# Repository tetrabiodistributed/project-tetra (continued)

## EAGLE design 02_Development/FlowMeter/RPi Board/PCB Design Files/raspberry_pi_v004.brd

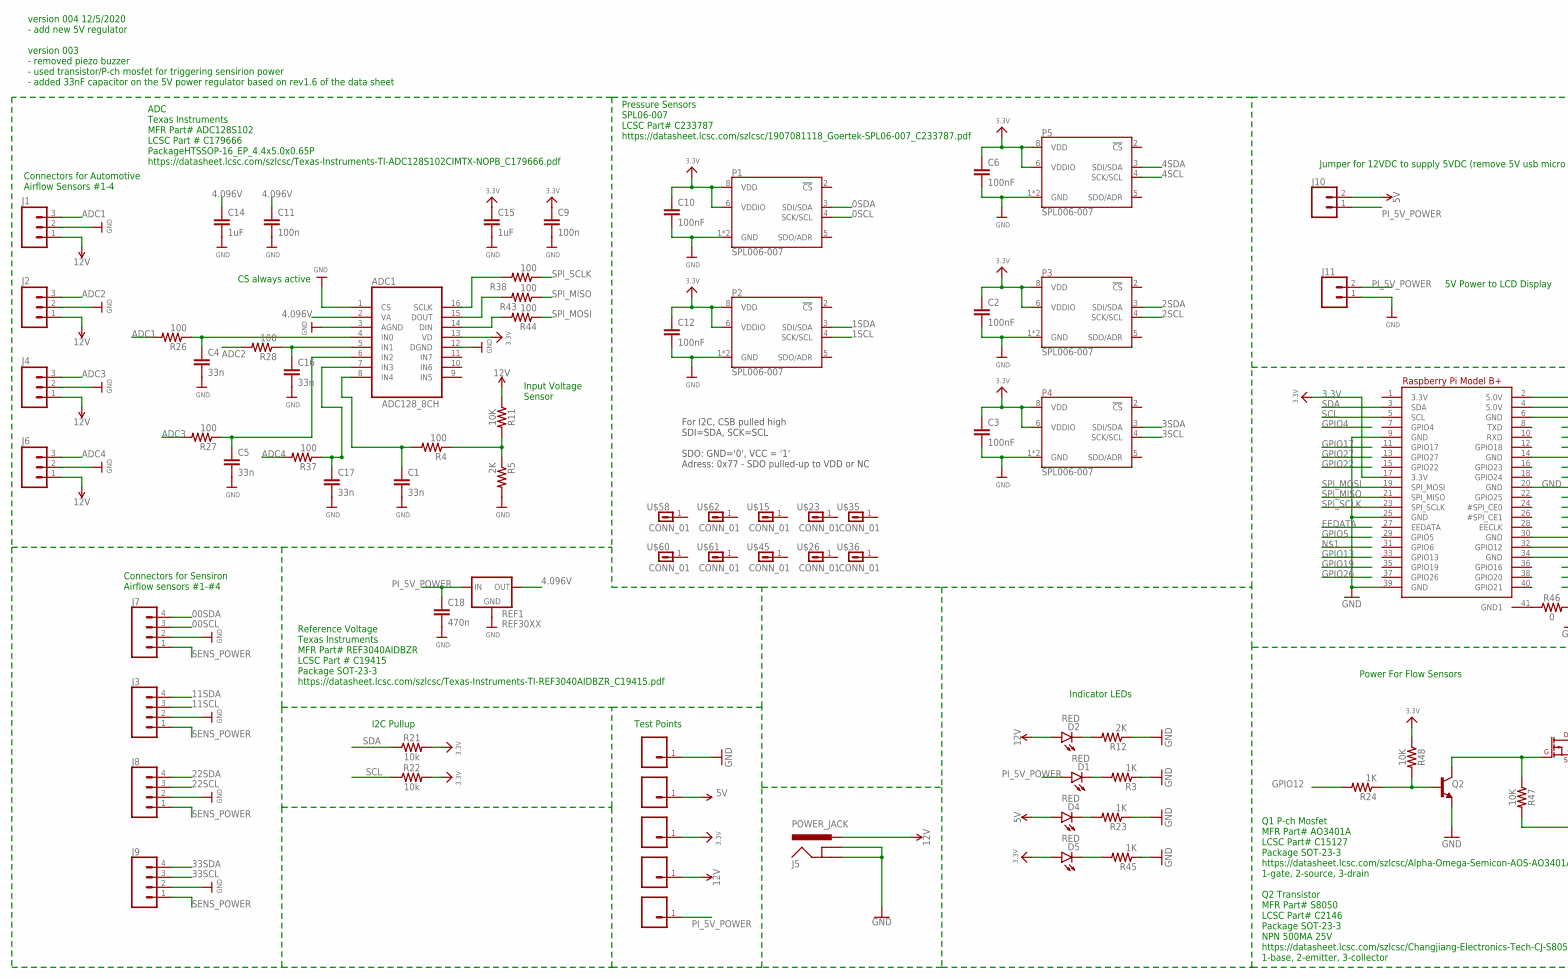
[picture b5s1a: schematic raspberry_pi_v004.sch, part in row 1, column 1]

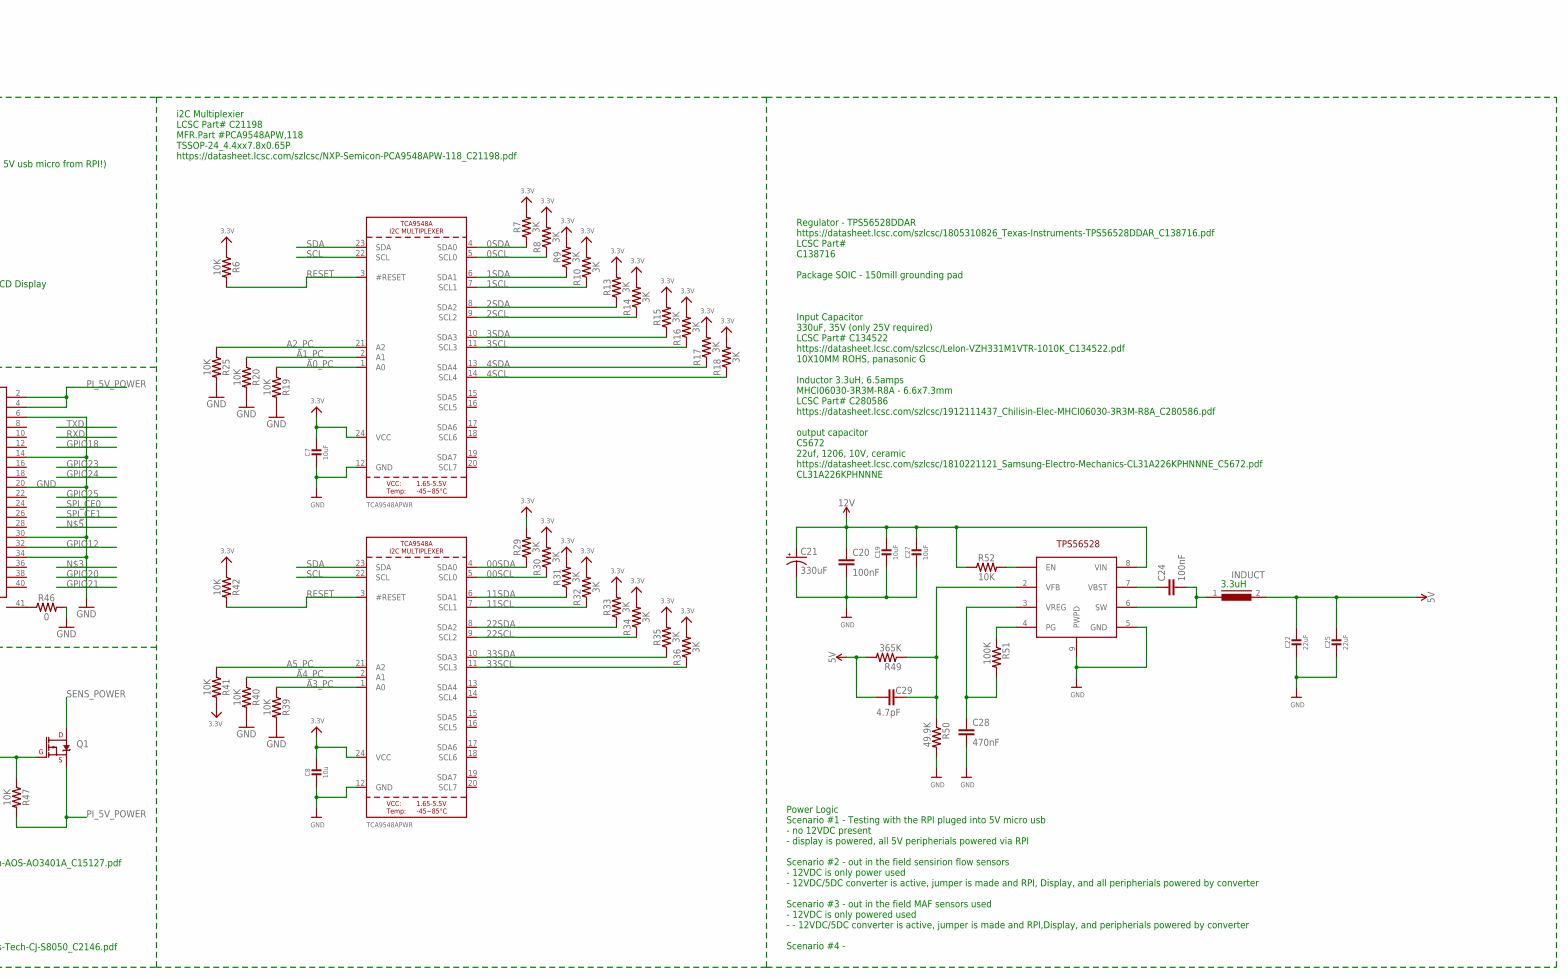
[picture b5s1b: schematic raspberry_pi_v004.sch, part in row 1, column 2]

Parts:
ADC1: ADC128_8CH; TSSOP16
C1, C4, C5, C16, C17: 33n; 0805
C2, C3, C6, C10, C12, C20, C24: 100nF; 0805
C7, C19, C27: 10uF; 0805-NO
C8: 10u; 0805-NO
C9, C11: 100n; 0805
C14, C15: 1uF; 0805
C18: 470n; 0805
C21: 330uF; PANASONIC_G
C22, C25: 22uF; _1206
C28: 470nF; 0805
C29: 4.7pF; 0603
D1, D2, D4, D5: RED; LED-1206
INDUCT: INDUCTOR_6.6_7.3
J1, J2, J4, J6: M03SCREW; SCREWTERMINAL-3.5MM-3
J3, J7, J8, J9: CONN_043.5MM_RA; 1X04_3.5MM_RA
J5: POWER_JACK; POWER_JACK_PTH
J10: CONN_02; 1X02
J11: CONN_025MM; SCREWTERMINAL-5MM-2
P1, P2, P3, P4, P5: SPL006-007; LGA-8-2.5X2.0
Q1: 4.3A/20V/54mΩ; SOT23-3
Q2: 500mA/300V; SOT23-3
R3, R23, R24, R45: 1K; 0805
R4, R26, R27, R28, R37, R38, R43, R44: 100; 0805
R5, R12: 2K; 0805
R6, R11, R19, R20, R25, R39, R40, R41, R42, R47, R48, R52: 10K; 0805
R7, R8, R9, R10, R13, R14, R15, R16, R17, R18, R29, R30, R31, R32, R33, R34, R35, R36: 3K; 0805
R21, R22: 10k; 0805
R46: 0; 0805
R49: 365K; 0805
R50: 49.9K; 0805
R51: 100K; 0805
REF1: REF30XX; SOT23-3
RPI2: MICROBUILDER_RASPBERRYPI_BPLUS_HATSLOTS; MICROBUILDER_PI_HAT_SLOTS
TPS: TPS56528; SOIC8_POWER
U6, U7: TCA9548APWR; TSSOP24
U$15, U$23, U$26, U$35, U$36, U$45, U$58, U$60, U$61, U$62: CONN_01; 1X01-#6_MACHINE
U$20, U$31, U$40, U$59, U$64: CONN_0138MILL; 1X01-40MILL

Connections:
0SCL: P1.4 (SCK/SCL), R8.1, U6.5 (SCL0)
00SCL: J7.3, R30.1, U7.5 (SCL0)
0SDA: P1.3 (SDI/SDA), R7.1, U6.4 (SDA0)
00SDA: J7.4, R29.1, U7.4 (SDA0)
1SCL: P2.4 (SCK/SCL), R10.1, U6.7 (SCL1)
1SDA: P2.3 (SDI/SDA), R9.1, U6.6 (SDA1)
2SCL: P3.4 (SCK/SCL), R14.1, U6.9 (SCL2)
2SDA: P3.3 (SDI/SDA), R13.1, U6.8 (SDA2)
3.3V: ADC1.13 (VD), C2.1, C3.1, C6.1, C7.1, C8.1, C9.1, C10.1, C12.1, C15.1, D5.A, P1.6 (VDDIO), P1.8 (VDD), P2.6 (VDDIO), P2.8 (VDD), P3.6 (VDDIO), P3.8 (VDD), P4.6 (VDDIO), P4.8 (VDD), P5.6 (VDDIO), P5.8 (VDD), R6.1, R7.2, R8.2, R9.2, R10.2, R13.2, R14.2, R15.2, R16.2, R17.2, R18.2, R21.2, R22.2, R29.2, R30.2, R31.2, R32.2, R33.2, R34.2, R35.2, R36.2, R41.2, R42.1, R48.1, RPI2.17 (3.3V), U6.24 (VCC), U7.24 (VCC), U$20.1
3SCL: P4.4 (SCK/SCL), R16.1, U6.11 (SCL3)
3SDA: P4.3 (SDI/SDA), R15.1, U6.10 (SDA3)
4.096V: ADC1.2 (VA), C11.1, C14.1, REF1.2 (OUT)
4SCL: P5.4 (SCK/SCL), R18.1, U6.14 (SCL4)
4SDA: P5.3 (SDI/SDA), R17.1, U6.13 (SDA4)
5V: C22.1, C25.1, C29.1, D4.A, INDUCT.2, J10.2, R49.2, U$59.1
11SCL: J3.3, R32.1, U7.7 (SCL1)
11SDA: J3.4, R31.1, U7.6 (SDA1)
12V: C19.1, C20.1, C21.+, C27.1, D2.A, J1.1, J2.1, J4.1, J5.PWR, J6.1, R11.1, R52.1, TPS.8 (VIN), U$40.1
22SCL: J8.3, R34.1, U7.9 (SCL2)
22SDA: J8.4, R33.1, U7.8 (SDA2)
33SCL: J9.3, R36.1, U7.11 (SCL3)
33SDA: J9.4, R35.1, U7.10 (SDA3)
A0_PC: R19.1, U6.1 (A0)
A1_PC: R20.1, U6.2 (A1)
A2_PC: R25.1, U6.21 (A2)
A3_PC: R39.1, U7.1 (A0)
A4_PC: R40.1, U7.2 (A1)
A5_PC: R41.1, U7.21 (A2)
ADC1: J1.3, R26.2
ADC2: J2.3, R28.2
ADC3: J4.3, R27.2
ADC4: J6.3, R37.2
GND: ADC1.1 (CS), ADC1.3 (AGND), ADC1.12 (DGND), C1.2, C2.2, C3.2, C4.2, C5.2, C6.2, C7.2, C8.2, C9.2, C10.2, C11.2, C12.2, C14.2, C15.2, C16.2, C17.2, C18.2, C19.2, C20.2, C21.-, C22.2, C25.2, C27.2, C28.2, J1.2, J2.2, J3.2, J4.2, J5.GND, J5.GNDBREAK, J6.2, J7.2, J8.2, J9.2, J11.1, P1.1 (GND), P1.7 (GND), P2.1 (GND), P2.7 (GND), P3.1 (GND), P3.7 (GND), P4.1 (GND), P4.7 (GND), P5.1 (GND), P5.7 (GND), Q2.2 (E), R3.1, R5.2, R12.1, R19.2, R20.2, R23.1, R25.2, R39.2, R40.2, R45.1, R46.2, R50.2, REF1.3 (GND), RPI2.6 (GND), RPI2.9 (GND), RPI2.14 (GND), RPI2.20 (GND), RPI2.25 (GND), RPI2.30 (GND), RPI2.34 (GND), RPI2.39 (GND), TPS.5 (GND), TPS.9 (PWPD), U6.12 (GND), U7.12 (GND), U$31.1
GND1: R46.1, RPI2.41 (GND1)
GPIO12: R24.2, RPI2.32 (GPIO12)
unnamed: D2.C, R12.2
unnamed: C24.2, INDUCT.1, TPS.6 (SW)
unnamed: C28.1, R51.2, TPS.3 (VREG)
unnamed: D1.C, R3.2
unnamed: Q1.1 (G), Q2.3 (C), R47.1
unnamed: Q2.1 (B), R24.1, R48.2
unnamed: C29.2, R49.1, R50.1, TPS.2 (VFB)
unnamed: ADC1.8 (IN4), C1.1, R4.2
unnamed: R4.1, R5.1, R11.2
unnamed: C24.1, TPS.7 (VBST)
unnamed: D4.C, R23.2
unnamed: D5.C, R45.2
unnamed: R51.1, TPS.4 (PG)
unnamed: ADC1.4 (IN0), C4.1, R26.1
unnamed: ADC1.6 (IN2), C5.1, R27.1
unnamed: ADC1.5 (IN1), C16.1, R28.1
unnamed: ADC1.7 (IN3), C17.1, R37.1
unnamed: ADC1.16 (SCLK), R38.2
unnamed: ADC1.15 (DOUT), R43.2
unnamed: ADC1.14 (DIN), R44.2
unnamed: R52.2, TPS.1 (EN)
PI_5V_POWER: C18.1, D1.A, J10.1, J11.2, Q1.2 (S), R47.2, REF1.1 (IN), RPI2.2 (5.0V), RPI2.4 (5.0V), U$64.1
RESET: R6.2, R42.2, U6.3 (#RESET), U7.3 (#RESET)
SCL: R22.1, RPI2.5 (SCL), U6.22 (SCL), U7.22 (SCL)
SDA: R21.1, RPI2.3 (SDA), U6.23 (SDA), U7.23 (SDA)
SENS_POWER: J3.1, J7.1, J8.1, J9.1, Q1.3 (D)
SPI_MISO: R43.1, RPI2.21 (SPI_MISO)
SPI_MOSI: R44.1, RPI2.19 (SPI_MOSI)
SPI_SCLK: R38.1, RPI2.23 (SPI_SCLK)

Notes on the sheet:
I2C Pullup
Test Points
Indicator LEDs
Power For Flow Sensors
For I2C, CSB pulled high SDI=SDA, SCK=SCL SDO: GND='0', VCC = '1' Adress: 0x77 - SDO pulled-up to VDD or NC
Connectors for Automotive Airflow Sensors #1-4
Pressure Sensors SPL06-007 LCSC Part# C233787 https://datasheet.lcsc.com/szlcsc/1907081118_Goertek-SPL06-007_C233787.pdf
Connectors for Sensiron Airflow sensors #1-#4
CS always active
Regulator - TPS56528DDAR https://datasheet.lcsc.com/szlcsc/1805310826_Texas-Instruments-TPS56528DDAR_C138716.pdf LCSC Part# C138716 Package SOIC - 150mill grounding pad Input Capacitor 330uF, 35V (only 25V required) LCSC Part# C134522 https://datasheet.lcsc.com/szlcsc/Lelon-VZH331M1VTR-1010K_C13452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
i2C Multiplexier LCSC Part# C21198 MFR.Part #PCA9548APW,118 TSSOP-24_4.4xx7.8x0.65P https://datasheet.lcsc.com/szlcsc/NXP-Semicon-PCA9548APW-118_C21198.pdf
ADC Texas Instruments MFR Part# ADC128S102 LCSC Part # C179666 PackageHTSSOP-16_EP_4.4x5.0x0.65P https://datasheet.lcsc.com/szlcsc/Texas-Instruments-TI-ADC128S102CIMTX-NOPB_C179666.pdf
Reference Voltage Texas Instruments MFR Part# REF3040AIDBZR LCSC Part # C19415 Package SOT-23-3 https://datasheet.lcsc.com/szlcsc/Texas-Instruments-TI-REF3040AIDBZR_C19415.pdf
Q1 P-ch Mosfet MFR Part# AO3401A LCSC Part# C15127 Package SOT-23-3 https://datasheet.lcsc.com/szlcsc/Alpha-Omega-Semicon-AOS-AO3401A_C15127.pdf 1-gate, 2-source, 3-drain Q2 Transistor MFR Part# S8050 LCSC Part# C2146 Package SOT-23-3 NPN 500MA 25V https://datasheet.lcsc.com/szlcsc/Changjiang-Elect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
Input Voltage Sensor
Jumper for 12VDC to supply 5VDC (remove 5V usb micro from RPI!)
5V Power to LCD Display
Power Logic Scenario #1 - Testing with the RPI pluged into 5V micro usb - no 12VDC present - display is powered, all 5V peripherials powered via RPI Scenario #2 - out in the field sensirion flow sensors - 12VDC is only power used - 12VDC/5DC converter is active, jumper is made and RPI, Display, and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
version 004 12/5/2020 - add new 5V regulator version 003 - removed piezo buzzer - used transistor/P-ch mosfet for triggering sensirion power - added 33nF capacitor on the 5V power regulator based on rev1.6 of the data sheet
3.3uH

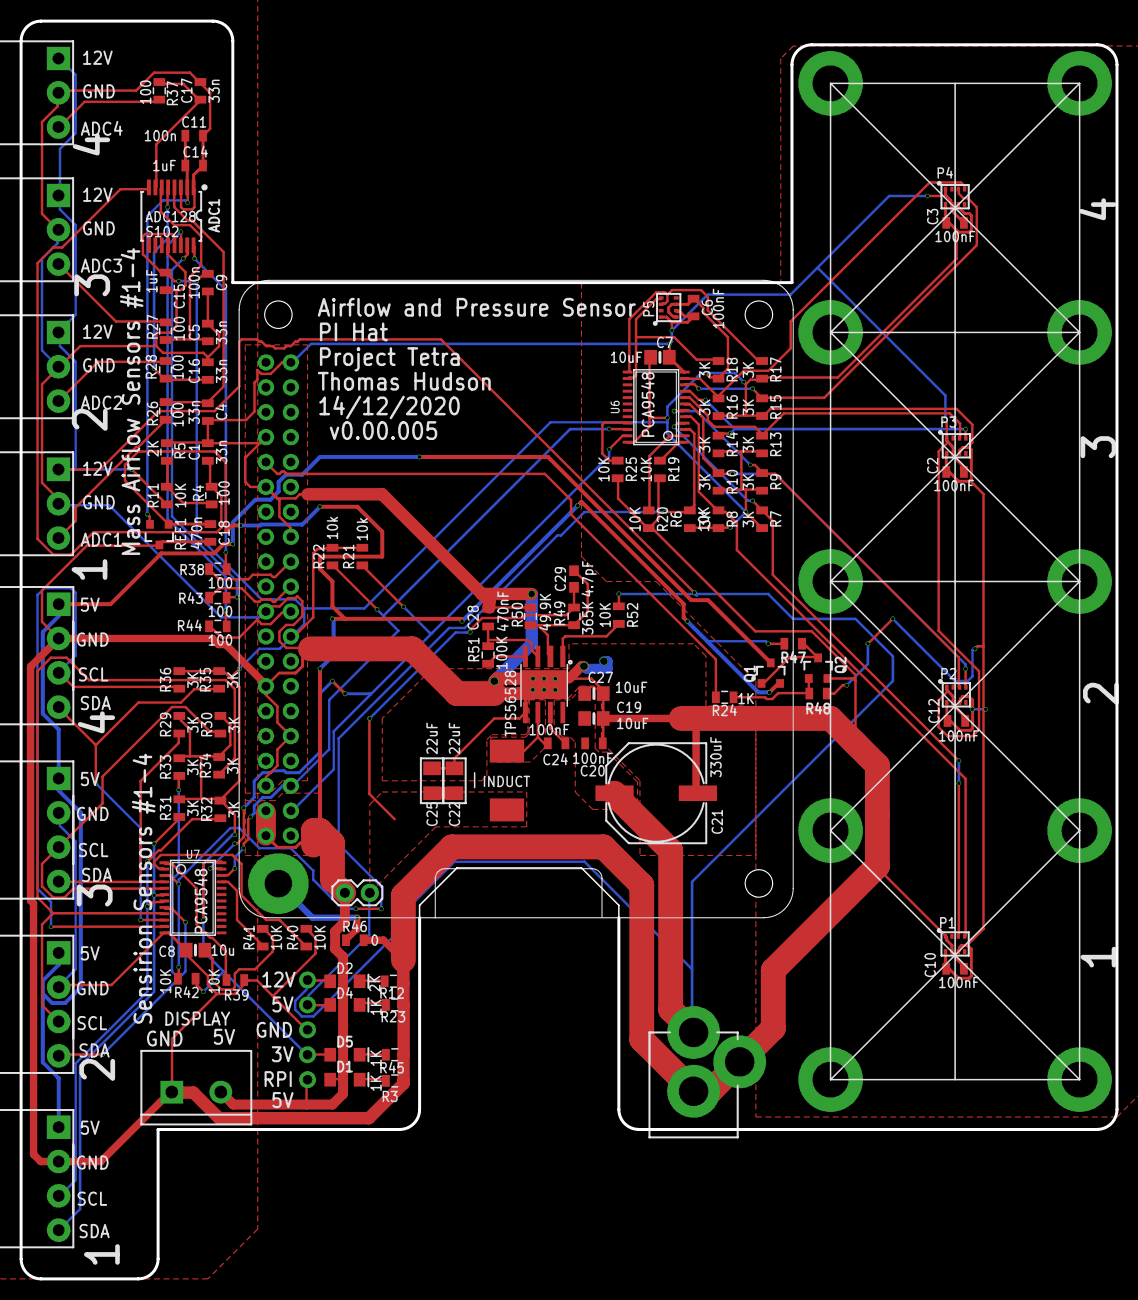
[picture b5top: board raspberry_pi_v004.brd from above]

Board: 2 copper layers, 111.8 x 128.3 mm, 120 parts (0 on the bottom side), 64 nets.

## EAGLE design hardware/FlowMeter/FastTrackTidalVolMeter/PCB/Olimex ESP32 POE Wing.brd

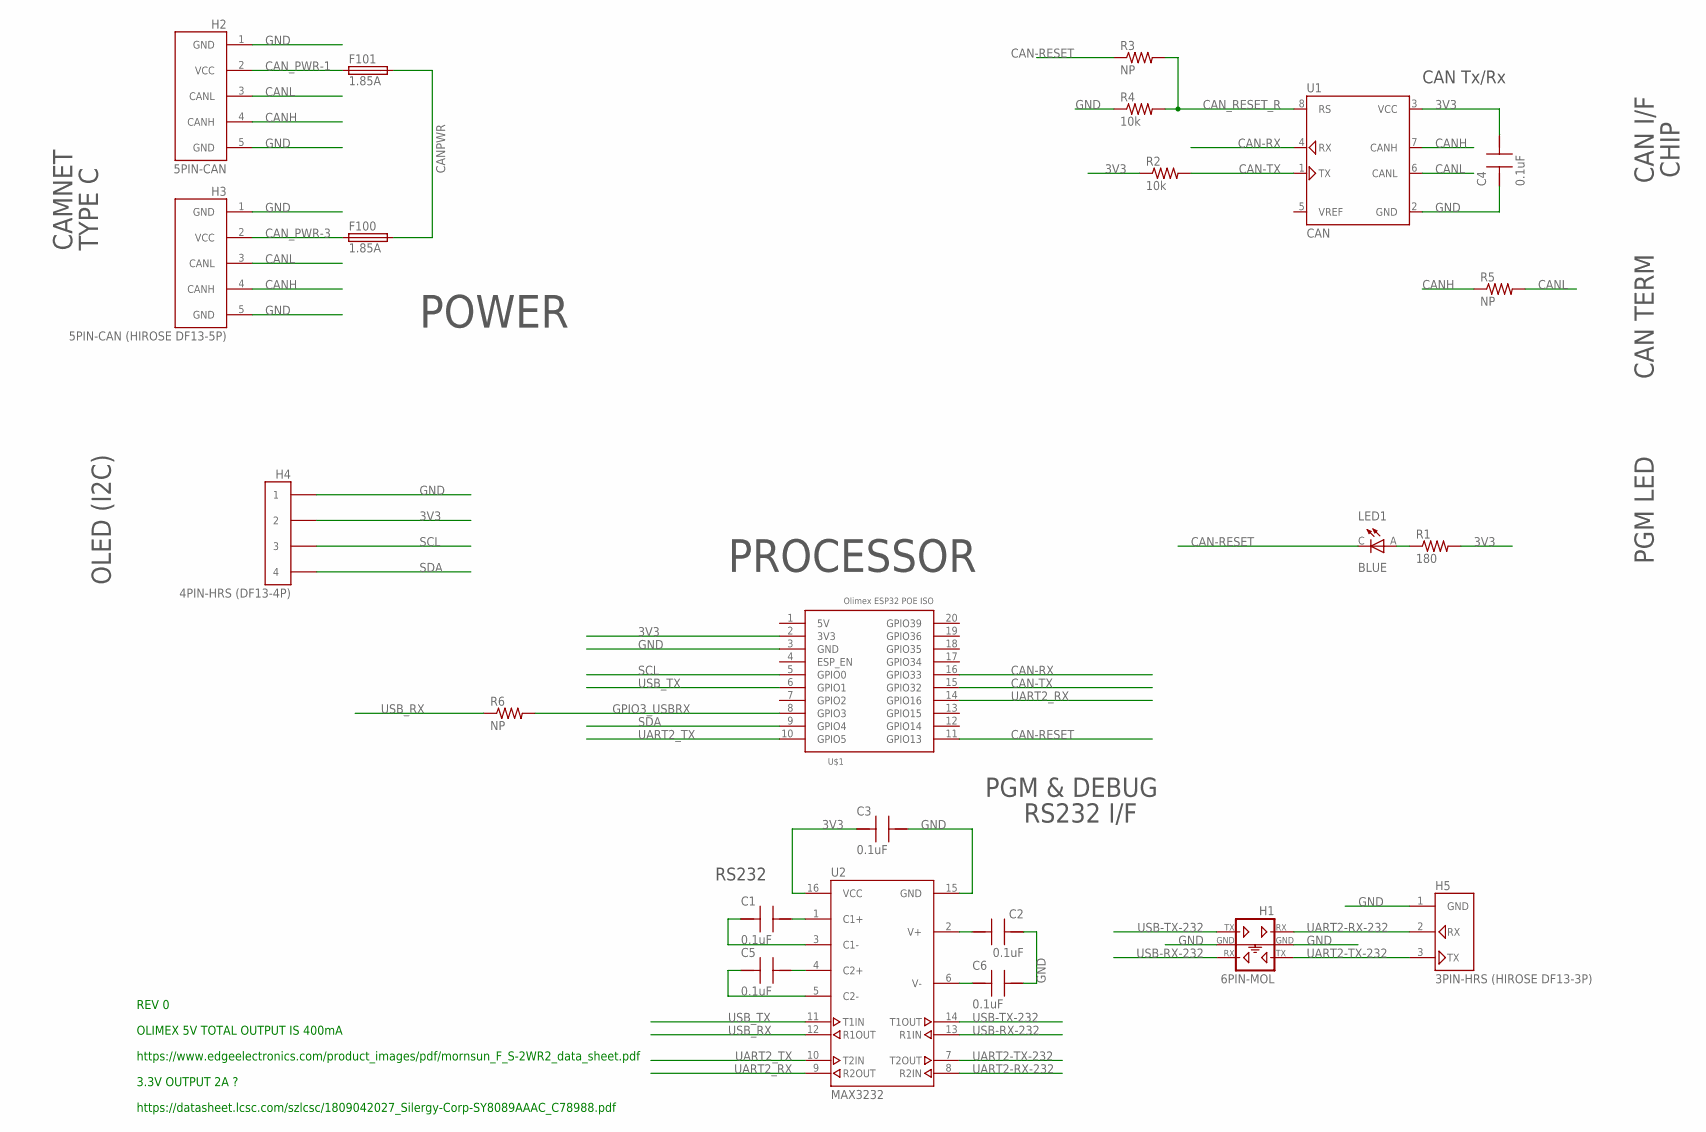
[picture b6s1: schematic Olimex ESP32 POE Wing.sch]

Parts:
C1, C2, C3, C4, C5, C6: 0.1uF; C0805
F100, F101: 1.85A; 2920
H1: 6PIN-MOL; 87831-0620
H2: 5PIN-CAN; DF13-5P-1.25DSA
H3: 5PIN-CAN (HIROSE DF13-5P); DF13-5P-1.25DSA
H4: 4PIN-HRS (DF13-4P); DF13-4P-1.25DSA
H5: 3PIN-HRS (HIROSE DF13-3P); DF13-3P-1.25DSA
LED1: BLUE; CHIPLED_0805
R1: 180; R0805
R2, R4: 10k; R0805
R3, R5, R6: NP; R0805
U1: CAN; SO-08
U2: MAX3232; TSSOP16
U$1: OLIMEX_POE_ISOPOEISO; OLIMEX_POE_ISO

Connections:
3V3: C3.2 (-), C4.1 (+), H4.2, R1.2, R2.1, U1.3 (VCC), U2.16 (VCC), U$1.2 (3V3)
5V: U$1.1 (5V)
BLUEX: LED1.A, R1.1
C1+: C1.1 (+), U2.1 (C1+)
C1-: C1.2 (-), U2.3 (C1-)
C2+: C5.1 (+), U2.4 (C2+)
C2-: C5.2 (-), U2.5 (C2-)
CAN-RESET: LED1.C, R3.1, U$1.11 (GPIO13)
CAN-RX: U1.4 (RX), U$1.16 (GPIO33)
CAN-TX: R2.2, U1.1 (TX), U$1.15 (GPIO32)
CANH: H2.4 (CANH), H3.4 (CANH), R5.1, U1.7 (CANH)
CANL: H2.3 (CANL), H3.3 (CANL), R5.2, U1.6 (CANL)
CANPWR: F100.P2 (2), F101.P2 (2)
CAN_PWR-1: F101.P1 (1), H2.2 (VCC)
CAN_PWR-3: F100.P1 (1), H3.2 (VCC)
CAN_RESET_R: R3.2, R4.2, U1.8 (RS)
GND: C2.2 (-), C3.1 (+), C4.2 (-), C6.1 (+), H1.3, H1.4, H2.1 (GND), H2.5 (GND), H3.1 (GND), H3.5 (GND), H4.1, H5.1 (GND), R4.1, U1.2 (GND), U2.15 (GND), U$1.3 (GND)
GPIO3_USBRX: R6.2, U$1.8 (GPIO3)
SCL: H4.3, U$1.5 (GPIO0)
SDA: H4.4, U$1.9 (GPIO4)
UART2-RX-232: H1.1, H5.2 (RX), U2.8 (R2IN)
UART2-TX-232: H1.5, H5.3 (TX), U2.7 (T2OUT)
UART2_RX: U2.9 (R2OUT), U$1.14 (GPIO16)
UART2_TX: U2.10 (T2IN), U$1.10 (GPIO5)
USB-RX-232: H1.6, U2.13 (R1IN)
USB-TX-232: H1.2, U2.14 (T1OUT)
USB_RX: R6.1, U2.12 (R1OUT)
USB_TX: U2.11 (T1IN), U$1.6 (GPIO1)
V+: C2.1 (+), U2.2 (V+)
V-: C6.2 (-), U2.6 (V-)

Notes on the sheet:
PROCESSOR
RS232
CAN TERM
CAN Tx/Rx
PGM LED
CAN I/F
CHIP
RS232 I/F
PGM & DEBUG
POWER
TYPE C
CAMNET
OLED (I2C)
OLIMEX 5V TOTAL OUTPUT IS 400mA
https://www.edgeelectronics.com/product_images/pdf/mornsun_F_S-2WR2_data_sheet.pdf
REV 0
3.3V OUTPUT 2A ?
https://datasheet.lcsc.com/szlcsc/1809042027_Silergy-Corp-SY8089AAAC_C78988.pdf

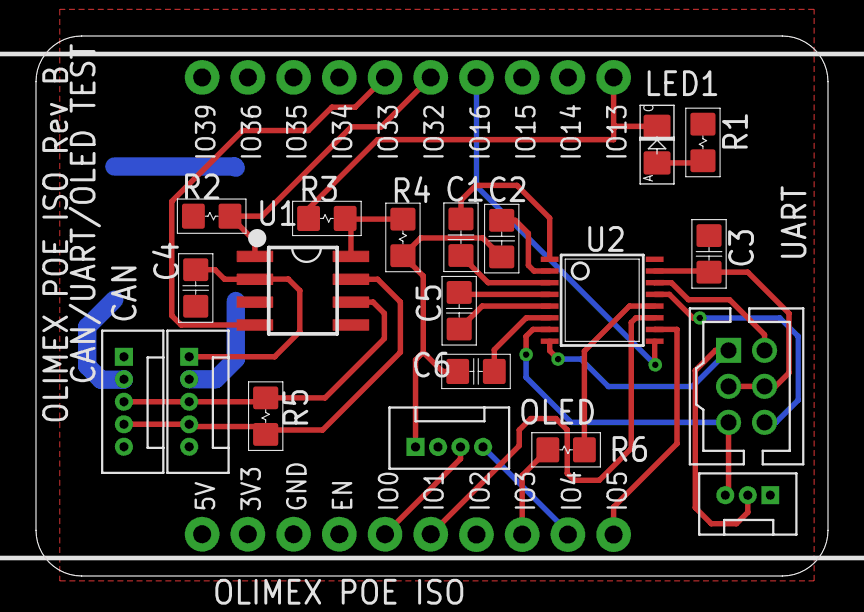
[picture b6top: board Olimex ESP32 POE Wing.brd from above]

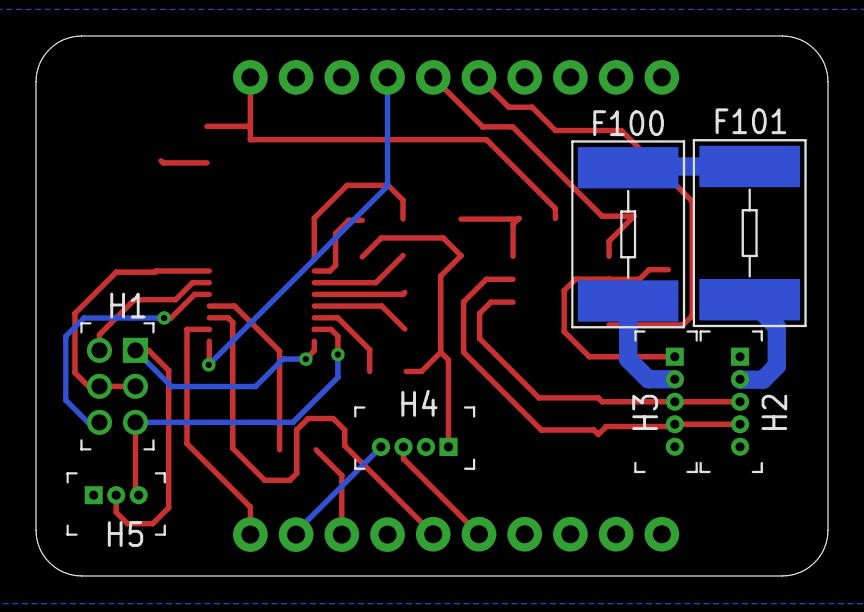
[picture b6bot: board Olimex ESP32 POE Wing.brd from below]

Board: 2 copper layers, 44.0 x 30.0 mm, 23 parts (2 on the bottom side), 29 nets.

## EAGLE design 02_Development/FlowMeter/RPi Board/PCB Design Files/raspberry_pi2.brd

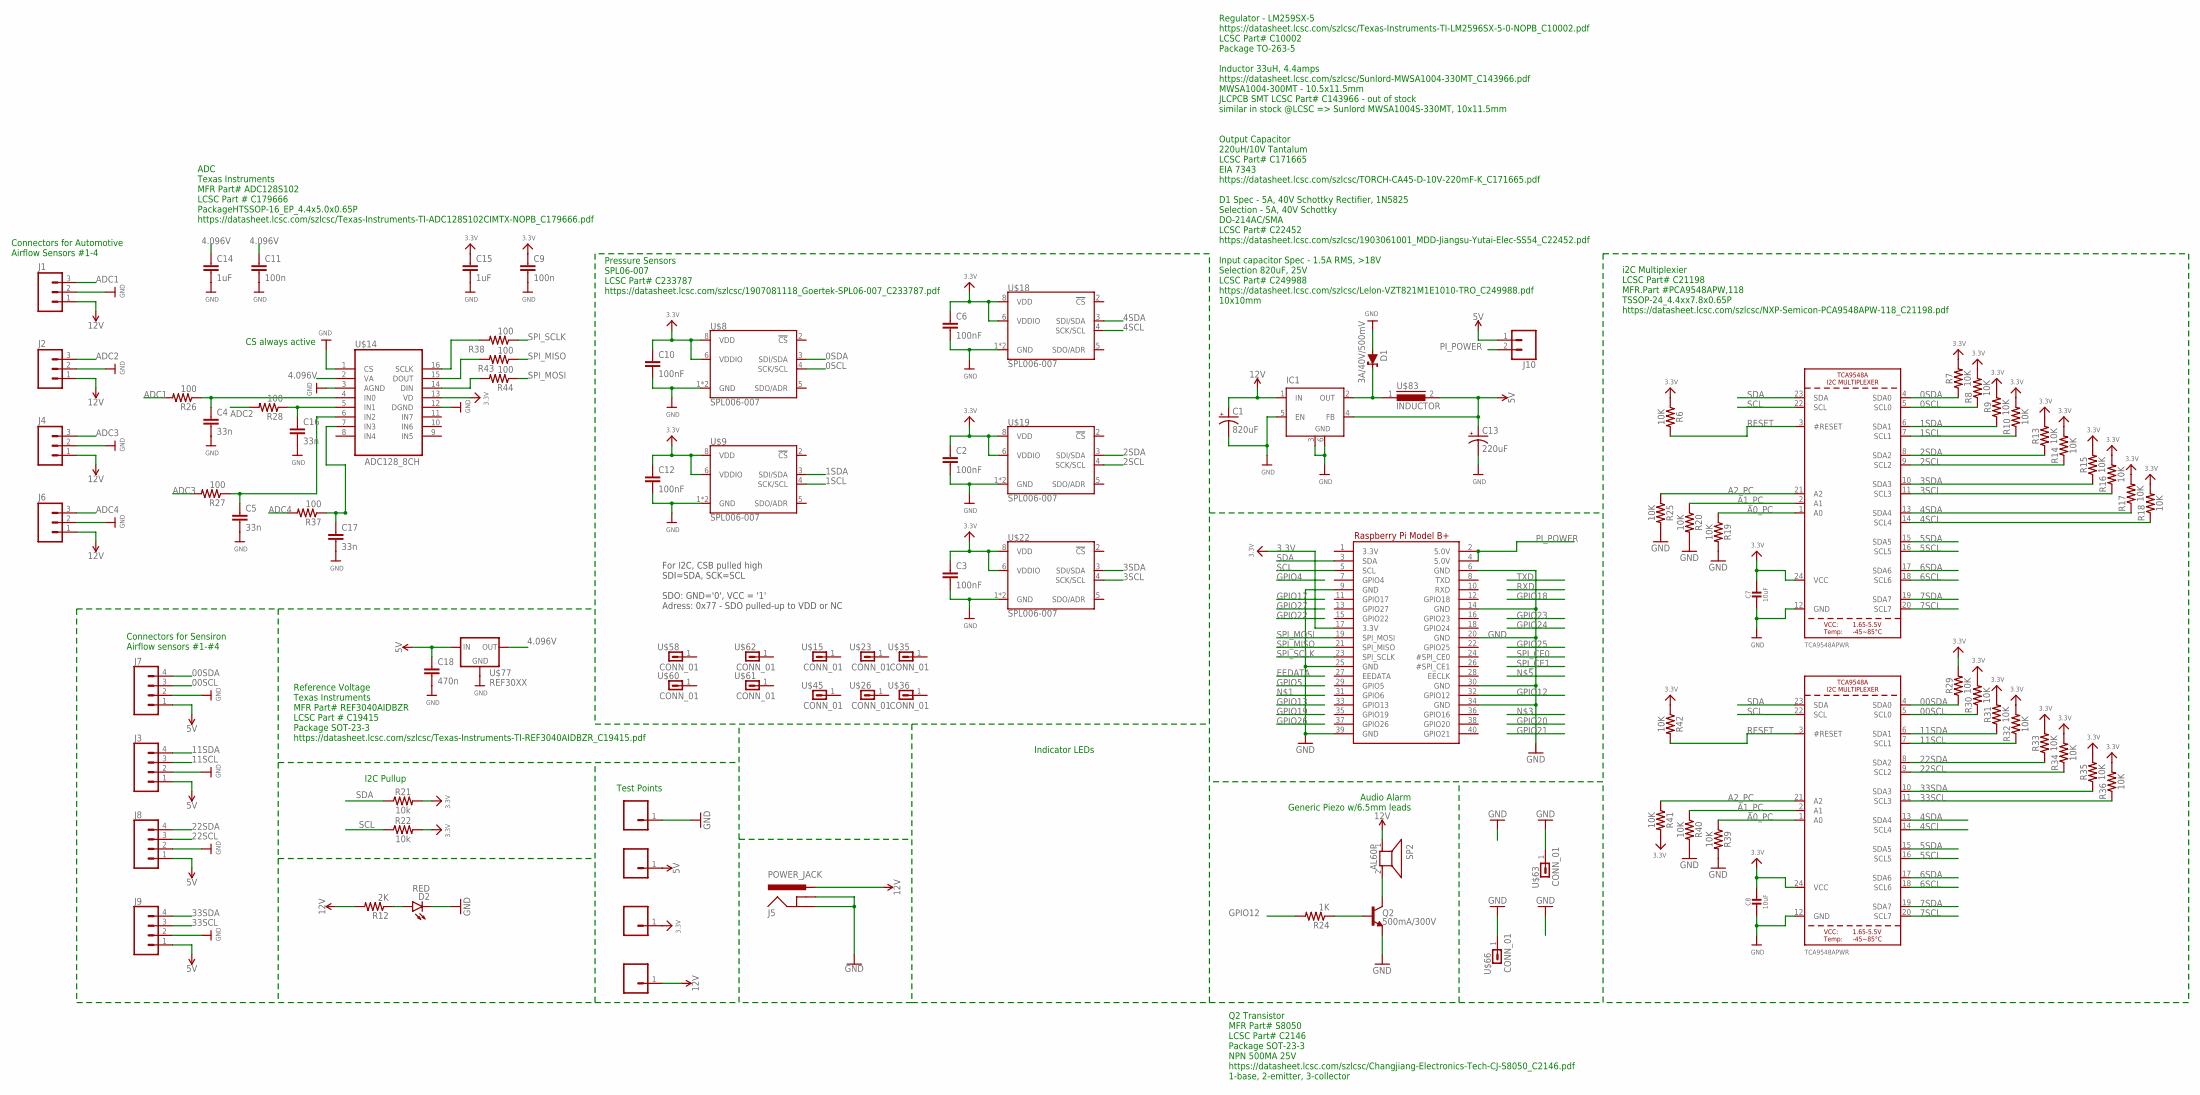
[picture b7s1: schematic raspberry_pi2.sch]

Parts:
C1: 820uF; PANASONIC_G
C2, C3, C6, C10, C12: 100nF; 0805
C4, C5, C16, C17: 33n; 0805
C7, C8: 10uF; 0805-NO
C9, C11: 100n; 0805
C13: 220uF; EIA7343
C14, C15: 1uF; 0805
C18: 470n; 0805
D1: 3A/40V/500mV; SMA-DIODE
D2: RED; LED-1206
IC1: LM2596S; TO263-5
J1, J2, J4, J6: M03SCREW; SCREWTERMINAL-3.5MM-3
J3, J7, J8, J9: CONN_043.5MM_RA; 1X04_3.5MM_RA
J5: POWER_JACK; POWER_JACK_PTH
J10: CONN_02; 1X02
Q2: 500mA/300V; SOT23-3
R6, R7, R8, R9, R10, R13, R14, R15, R16, R17, R18, R19, R20, R25, R29, R30, R31, R32, R33, R34, R35, R36, R39, R40, R41, R42: 10K; 0805
R12: 2K; 0805
R21, R22: 10k; 0805
R24: 1K; 0805
R26, R27, R28, R37, R38, R43, R44: 100; 0805
RPI1: MICROBUILDER_RASPBERRYPI_BPLUS_HATNOSLOTS_1; MICROBUILDER_PI_HAT_NOSLOTS
SP2: AL60P
U6, U7: TCA9548APWR; TSSOP24
U$8, U$9, U$18, U$19, U$22: SPL006-007; LGA-8-2.5X2.0
U$14: ADC128_8CH; TSSOP16
U$15, U$23, U$26, U$35, U$36, U$45, U$58, U$60, U$61, U$62, U$63, U$66: CONN_01; 1X01-#6_MACHINE
U$20, U$31, U$40, U$59: CONN_0138MILL; 1X01-40MILL
U$77: REF30XX; SOT23-3
U$83: INDUCTOR; INDUCTOR_10.5X11.5

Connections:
0SCL: R8.1, U6.5 (SCL0), U$8.4 (SCK/SCL)
00SCL: J7.3, R30.1, U7.5 (SCL0)
0SDA: R7.1, U6.4 (SDA0), U$8.3 (SDI/SDA)
00SDA: J7.4, R29.1, U7.4 (SDA0)
1SCL: R10.1, U6.7 (SCL1), U$9.4 (SCK/SCL)
1SDA: R9.1, U6.6 (SDA1), U$9.3 (SDI/SDA)
2SCL: R14.1, U6.9 (SCL2), U$19.4 (SCK/SCL)
2SDA: R13.1, U6.8 (SDA2), U$19.3 (SDI/SDA)
3.3V: C2.1, C3.1, C6.1, C7.1, C8.1, C9.1, C10.1, C12.1, C15.1, R6.1, R7.2, R8.2, R9.2, R10.2, R13.2, R14.2, R15.2, R16.2, R17.2, R18.2, R21.2, R22.2, R29.2, R30.2, R31.2, R32.2, R33.2, R34.2, R35.2, R36.2, R41.2, R42.1, RPI1.17 (3.3V), U6.24 (VCC), U7.24 (VCC), U$8.6 (VDDIO), U$8.8 (VDD), U$9.6 (VDDIO), U$9.8 (VDD), U$14.13 (VD), U$18.6 (VDDIO), U$18.8 (VDD), U$19.6 (VDDIO), U$19.8 (VDD), U$20.1, U$22.6 (VDDIO), U$22.8 (VDD)
3SCL: R16.1, U6.11 (SCL3), U$22.4 (SCK/SCL)
3SDA: R15.1, U6.10 (SDA3), U$22.3 (SDI/SDA)
4.096V: C11.1, C14.1, U$14.2 (VA), U$77.2 (OUT)
4SCL: R18.1, U6.14 (SCL4), U7.14 (SCL4), U$18.4 (SCK/SCL)
4SDA: R17.1, U6.13 (SDA4), U7.13 (SDA4), U$18.3 (SDI/SDA)
5SCL: U6.16 (SCL5), U7.16 (SCL5)
5SDA: U6.15 (SDA5), U7.15 (SDA5)
5V: C13.A (+), C18.1, IC1.4 (FB), J3.1, J7.1, J8.1, J9.1, J10.1, U$59.1, U$77.1 (IN), U$83.2
6SCL: U6.18 (SCL6), U7.18 (SCL6)
6SDA: U6.17 (SDA6), U7.17 (SDA6)
7SCL: U6.20 (SCL7), U7.20 (SCL7)
7SDA: U6.19 (SDA7), U7.19 (SDA7)
11SCL: J3.3, R32.1, U7.7 (SCL1)
11SDA: J3.4, R31.1, U7.6 (SDA1)
12V: C1.+, IC1.1 (IN), J1.1, J2.1, J4.1, J5.PWR, J6.1, R12.2, SP2.1, U$40.1
22SCL: J8.3, R34.1, U7.9 (SCL2)
22SDA: J8.4, R33.1, U7.8 (SDA2)
33SCL: J9.3, R36.1, U7.11 (SCL3)
33SDA: J9.4, R35.1, U7.10 (SDA3)
A0_PC: R19.1, R39.1, U6.1 (A0), U7.1 (A0)
A1_PC: R20.1, R40.1, U6.2 (A1), U7.2 (A1)
A2_PC: R25.1, R41.1, U6.21 (A2), U7.21 (A2)
ADC1: J1.3, R26.2
ADC2: J2.3, R28.2
ADC3: J4.3, R27.2
ADC4: J6.3, R37.2
GND: C1.-, C2.2, C3.2, C4.2, C5.2, C6.2, C7.2, C8.2, C9.2, C10.2, C11.2, C12.2, C13.C (-), C14.2, C15.2, C16.2, C17.2, C18.2, D1.A, D2.C, IC1.3 (GND), IC1.5 (EN), IC1.6 (GND), J1.2, J2.2, J3.2, J4.2, J5.GND, J5.GNDBREAK, J6.2, J7.2, J8.2, J9.2, Q2.2 (E), R19.2, R20.2, R25.2, R39.2, R40.2, RPI1.6 (GND), RPI1.9 (GND), RPI1.14 (GND), RPI1.20 (GND), RPI1.25 (GND), RPI1.30 (GND), RPI1.34 (GND), RPI1.39 (GND), U6.12 (GND), U7.12 (GND), U$8.1 (GND), U$8.7 (GND), U$9.1 (GND), U$9.7 (GND), U$14.1 (CS), U$14.3 (AGND), U$14.12 (DGND), U$18.1 (GND), U$18.7 (GND), U$19.1 (GND), U$19.7 (GND), U$22.1 (GND), U$22.7 (GND), U$31.1, U$63.1, U$66.1, U$77.3 (GND)
GPIO12: R24.2, RPI1.32 (GPIO12)
unnamed: D2.A, R12.1
unnamed: Q2.3 (C), SP2.2
unnamed: Q2.1 (B), R24.1
unnamed: C4.1, R26.1, U$14.4 (IN0)
unnamed: C5.1, R27.1, U$14.6 (IN2)
unnamed: C16.1, R28.1, U$14.5 (IN1)
unnamed: D1.C, IC1.2 (OUT), U$83.1
unnamed: C17.1, R37.1, U$14.7 (IN3)
unnamed: R38.2, U$14.16 (SCLK)
unnamed: R43.2, U$14.15 (DOUT)
unnamed: R44.2, U$14.14 (DIN)
PI_POWER: J10.2, RPI1.2 (5.0V), RPI1.4 (5.0V)
RESET: R6.2, R42.2, U6.3 (#RESET), U7.3 (#RESET)
SCL: R22.1, RPI1.5 (SCL), U6.22 (SCL), U7.22 (SCL)
SDA: R21.1, RPI1.3 (SDA), U6.23 (SDA), U7.23 (SDA)
SPI_MISO: R43.1, RPI1.21 (SPI_MISO)
SPI_MOSI: R44.1, RPI1.19 (SPI_MOSI)
SPI_SCLK: R38.1, RPI1.23 (SPI_SCLK)

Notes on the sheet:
I2C Pullup
Test Points
Indicator LEDs
Audio Alarm Generic Piezo w/6.5mm leads
For I2C, CSB pulled high SDI=SDA, SCK=SCL SDO: GND='0', VCC = '1' Adress: 0x77 - SDO pulled-up to VDD or NC
Connectors for Automotive Airflow Sensors #1-4
Pressure Sensors SPL06-007 LCSC Part# C233787 https://datasheet.lcsc.com/szlcsc/1907081118_Goertek-SPL06-007_C233787.pdf
Connectors for Sensiron Airflow sensors #1-#4
CS always active
Regulator - LM259SX-5 https://datasheet.lcsc.com/szlcsc/Texas-Instruments-TI-LM2596SX-5-0-NOPB_C10002.pdf LCSC Part# C10002 Package TO-263-5 Inductor 33uH, 4.4amps https://datasheet.lcsc.com/szlcsc/Sunlord-MWSA1004-330MT_C143966.pdf MWSA1004-300MT - 10.5x11.5mm JLCPCB SMT LCSC Part# C143966 - out o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
i2C Multiplexier LCSC Part# C21198 MFR.Part #PCA9548APW,118 TSSOP-24_4.4xx7.8x0.65P https://datasheet.lcsc.com/szlcsc/NXP-Semicon-PCA9548APW-118_C21198.pdf
ADC Texas Instruments MFR Part# ADC128S102 LCSC Part # C179666 PackageHTSSOP-16_EP_4.4x5.0x0.65P https://datasheet.lcsc.com/szlcsc/Texas-Instruments-TI-ADC128S102CIMTX-NOPB_C179666.pdf
Reference Voltage Texas Instruments MFR Part# REF3040AIDBZR LCSC Part # C19415 Package SOT-23-3 https://datasheet.lcsc.com/szlcsc/Texas-Instruments-TI-REF3040AIDBZR_C19415.pdf
Q2 Transistor MFR Part# S8050 LCSC Part# C2146 Package SOT-23-3 NPN 500MA 25V https://datasheet.lcsc.com/szlcsc/Changjiang-Electronics-Tech-CJ-S8050_C2146.pdf 1-base, 2-emitter, 3-collector

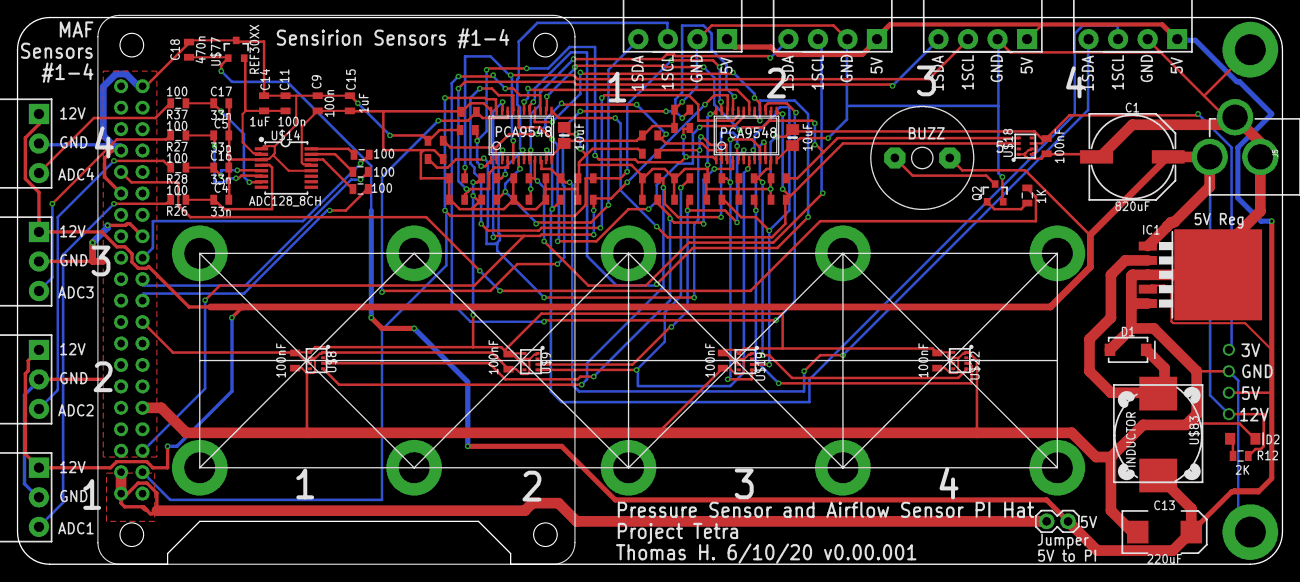
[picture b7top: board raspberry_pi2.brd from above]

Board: 2 copper layers, 149.9 x 64.8 mm, 97 parts (0 on the bottom side), 55 nets.

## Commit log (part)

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2020-04-05 clean up
2020-04-05 cleanup
2020-04-07 added 2 way splitter + one way valve
2020-04-07 Documentation dump
    First set of schematics, documentation of the April 2 2020 test
2020-04-07 added rev5 One way valve
2020-04-07 changed name of inspiratory 2-way splitter
2020-04-08 Adding 1 way valve for 3/4" PVC Slip
2020-04-13 Added custom stopper for globe valve
2020-04-15 relocate files for organization
2020-04-22 connector
2020-04-27 Clearance update
    Request for splitters to be updated to accommodate 2" diameter filter installed on each outlet of splitter. Remodeled parts to work with Solidworks 2018. Note that expiratory splitter as previously c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
2020-04-30 Adding HEVS Peep Body
2020-05-12 remove depreciated part drawings
2020-05-14 adding hotwire and pressure sensor
2020-05-20 Cap label changes and & stl
2020-05-20 Updated Valve Head
2020-05-22 add submodule for docsy theme
    - docsy theme available at https://github.com/google/docsy.git
2020-05-22 add github action for deploying to gh-pages
    - use latest example workflow from https://discourse.gohugo.io/t/deploy-hugo-project-to-github-pages-with-github-actions/20725/5
2020-05-22 install node modules in deploy action
2020-05-22 Use peaceiris recommended workflow
    - https://github.com/peaceiris/actions-hugo#%EF%B8%8F-create-your-workflow
2020-05-25 set canonifyURL & baseURL in config.yml
2020-05-25 Rename all instances of Goldydocs to Project Tetra
2020-05-27 replace links w/ helpfulengineering/project-tetra
    replace "github.com/google/docsy-example" w/ "github.com/helpfulengineering/project-tetra"
2020-05-27 Revise doc section descriptions
2020-05-27 fix featured-background.jpg not showing
    - set 'canonifyURLs = false
2020-05-28 mislabeled
2020-05-29 Update README
    - Replace content verbiage w/ meta description
    - add section for Prerequisites, Cloning, and Running locally
2020-05-29 add 'Components in Development' to Explanations
2020-05-31 Update landing page w/ executive summary
    - add executive summary
    - remove unused boilerplate verbiage
    - add link to contributing guide
    - replace Norsk w/ Spanish
2020-06-02 Update featured background
    - replace blueberry oatmeal w/ tetra v2.4 rendering
2020-06-03 deploy: c11baa0482b4661af9ea9f74459eb1e2146d1723
2020-06-04 Fix broken link to contribution guide on main page
2020-06-04 Added the 5 way splitter
2020-06-04 deploy: 08efa6be0a02dd29107d644a1290bb455362315b
2020-06-04 v4-1 Tetra valve
    Design works with G-74 - Compression Spring from Century Spring Corp
    https://www.centuryspring.com/catalog/?page=product&cid=root&id=G-74CS
2020-06-04 Update and rename folder to Readme
2020-06-04 Tetra valve v4-2
2020-06-04 Updated getting started section
2020-06-04 updating the documentation to be the most recent, including removing peep valves and starting a parts/build guide
2020-06-04 saving current version
2020-06-04 Fixed images again after moving
2020-06-04 Update PEEP on overview
2020-06-04 Upadet iverview
    fix spelling
2020-06-04 Update title page
2020-06-09 Remove site content, update README
    - site content migrated to https://tetrabiodistributed.github.io/
2020-06-10 Cleaned up main-splitter
2020-06-12 removed lfs
2020-06-13 Added folders for RPi PCB
2020-06-14 committing the images to make error messages go away
    Added a tutorial on how to turn on the ventillator splitter
    fixed the How To Turn On tutorial's broken image URL and and bad 3rd-level list
2020-06-15 improved the language in the How To Turn On tutorial
2020-06-15 created a first version of the Tubing Data information screen
2020-06-17 removed the images from the pull request (hopefully)
2020-06-24 updated pcb design files
2020-06-29 add ibd-ventilator-splitter-assembly
2020-07-01 add ibd-electronic-sensing-system
2020-07-07 Manifold v2-0 STEP
2020-07-07 Manifold v2 SW-2018
2020-07-07 Rename Readme to Readme.md
2020-07-08 added an empty line at the end of all files
2020-07-08 Made the behave tests fit better with the idioms of that system, put the class in a dedicated module, made return a number instead of a generator
2020-07-08 updated behave tests based on Mark's notes
2020-07-08 changed the sensors module so it will read data from a file when it's not run on a raspberry pi and added the start of a behave test to verify that the Docker image works.
2020-07-09 Created a driver for the SPL06-007 pressure sensor. Does not yet pass correctness test.
2020-07-09 improved the pressure driver a bit (though it still returns wrong values) and added a script to find all i2c devices and documentation on the sensor
2020-07-09 moved the pressure driver to the new working directory
2020-07-09 renamed the problem files to something more clear to a non-case-sensitive file system
2020-07-10 wrote a driver for the flow sensor. It passes tests outside of hardware, but with hardware hasn't been verified yet. Also added an off-hardware version of I2CInterface
2020-07-10 changed the sensors module so it will read data from a file when it's not run on a raspberry pi and added the start of a behave test to verify that the Docker image works.
    moved directories for Display to 02_Development/Display
    Created a driver for the SPL06-007 pressure sensor. Does not yet pass correctness test.
    made the code closer to the data sheet, but the bug causing the incorrect pressure/temperature readings is at large.
    improved the pressure driver a bit (though it still returns wrong values) and added a script to find all i2c devices and documentation on the sensor
    moved the pressure driver to the new working directory
    retrieved some files that mysteriously dissapeared from g
2020-07-13 Adding piping complex STLs
    P-TET-000001-0
    P-TET-000002-0
    P-TET-000003-0
2020-07-14 MBSE-ify ventilator-splitter-assembly
    - rename ibd-ventilator-splitter-assembly.puml -> ibd-system-ventilator-splitter-assembly-airflow.puml
    - use !include to block-ify ventilator-splitter-assembly
    - rename ibd-electronic-sensing-system.puml -> ibd-system-electronic-sensing-system-dataflow.puml
2020-07-14 added more changes based on #52
2020-07-15 Adding FDM version of Pressure Manifold
2020-07-16 Remove redundant part
2020-07-17 Delete P-TET-000023-0.stl
    bad upload
2020-07-17 Updated corners with lip (#59)
2020-07-21 Fixed errors that came out of the test_sensors, changed the sampling for the board to command mode to save time.
2020-07-21 git somehow added a bunch of random garbage into half the files in my last push, so I've had to fix that.
2020-07-24 Fixed some stuff so the tests pass (except for the tests that rely on hardware configurations I don't have access to)
2020-07-28 Feature/drivers (#57)
    * Created a driver for the SPL06-007 pressure sensor. Does not yet pass correctness test.
    * made the code closer to the data sheet, but the bug causing the incorrect pressure/temperature readings is at large.
    * improved the pressure driver a bit (though it still returns wrong values) and added a script to find all i2c devices and documentation on the sensor
    * moved the pressure driver to the new working directory
    * retrieved some files that mysteriously dissapeared from git
    * renamed the problem files to something more clear to a non-case-sensitive file system
2020-07-29 updated the front end to look (mostly) like Hannah's drawing
2020-07-29 Updated based on Hannah's first notes
2020-07-29 Made the row headers wider
2020-07-30 Add files via upload
    Updated Tetra Plunger
2020-07-30 Add files via upload
    Re-exported Plunger
2020-07-31 Issue #98
2020-07-31 Issue #97
2020-07-31 added sensirion connector board
    eagle files and 3d renderings
2020-08-01 moved phoenix connector 5mm
    moved connector 5mm outboard
2020-08-04 moved phoenix connector
    on sensirion connector board... moved phoenic connector closer to pogo pins. current distance is 8.3mm or 0.33"
2020-08-05 Adding parts to be printed
2020-08-05 pcb_for_sensirion_connector (#114)
    move phoenix connector to be 8.4mm or 0.33" from pogo_pins
2020-08-24 remove system_model/ folder
    - system_model folder is being maintained in project-tetra-docs repo as of https://github.com/tetrabiodistributed/project-tetra-docs/commit/db0e2aeb8d7ff68d8685687295b12f4f1045cc6f
2020-08-26 Drawing template #95
    Files created by @mechatroniks-git for use as drawing templates for use with Alpha prototype
2020-08-31 Drawing template #95 (#127)
    Files created by @mechatroniks-git for use as drawing templates for use with Alpha prototype
2020-10-13 add new PCB v003 with updates
    - added hard reset for sensirion using p-channel moseft
    - added capacior per the updated cut sheet v1.6 for the 5V regulator
2020-10-18 beta testing parts
    Initial changes for beta updates of prototype, changes for parts:
    P-TET-000001
    P-TET-000002
    P-TET-000003
    P-TET-000018
    P-TET-000019
2020-10-21 Changed part numbers to remove duplicates and fit with current system
2020-11-09 Changed part numbers to remove duplicates and fit with current system (#137)
2020-11-24 Beta p1 (#143)
    * beta testing parts
    Initial changes for beta updates of prototype, changes for parts:
    P-TET-000001
    P-TET-000002
    P-TET-000003
    P-TET-000018
2020-11-24 Revert "Beta p1 (#143)"
    This reverts commit f96318b4aaa22900efba85e47ab331ddc2bdf8ed.
2020-12-08 updated capacitor
    changed C22 and C25 to 1206 footprint and specified 2mohm low ESR cap
2020-12-14 Next revision of PCB
    Changed I2C pullup resistors to 3Kohm
    General tidy up and fix of issues on the PCB. Tweaked some polygons to eliminate sharp corners, made some traces larger.
2020-12-16 Create READ ME BEFORE CONTINUING.md
    Added a cautionary text file to explain the issue with the automatically generated BOM and the incorrect resistor values being utilised.
2020-12-18 Adding in latest files
2021-01-01 Board ready for review
2021-01-04 v007 documentation updates & manufacturing files
2021-01-06 add fiducials & CAD step file, cleanup
2021-01-12 Added power jumper, redid all manufacturing files & BOMs
2021-01-13 sensor board updates
2021-01-15 Undeleting mechanical folders
2021-01-18 Adjusted board outline to be 20mm x 20mm for JLC Assembly
2021-02-01 Update to BOM for missing 40pin
2021-02-12 Updating license to a copy left version
    We were previously using a non copy left license so I am updating the license to be copy left
2021-03-03 Add manufacturing drawings
2021-03-05 Move everything to more appropriate folder
2021-07-08 Upload 12 mm push fit parts for manufacture
2021-08-21 Upload printable push fit adapters
    These adapters are compatible with 3/8" BSPT fittings and because Fusion 360 cannot model tapered threads were made by importing a part with 3/8" BSPT threads from McMaster-Carr, scaling them up in t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
2021-09-02 Update P-TET-000138-0.stl
    Update to bring valve seat in line with tetra valve
2021-09-07 Forgot to save
    oops
2021-09-14 Move files into more sensible place
2021-09-14 Create BOM.md
    Create first stab at bill of materials
2021-09-14 Remove old versions of adapters
    The iges and step files were only relevant when we were going to have the components machined. Now we are printing them they are surplus to requirements. The associated drawings have also been remove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
2021-09-14 Update BOM.md
    Added thread spec on stud
2021-09-14 Update BOM.md
    Removed component cost as it is unnecessary.
2021-09-15 Update BOM.md
    Add description of o ring standard.
